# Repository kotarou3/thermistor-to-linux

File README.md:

# Thermistor to Linux adapter

This project creates three thermistor inputs that can be read via the Linux
hwmon interface

It uses the MAX6698 chip for its 3 thermistor inputs, attached to an I2C-Tiny-USB
via I2C, which then attaches onto the system USB bus

I chose the MAX6698 because it was one of the few chips satisfying:
 - Already has a Linux hwmon driver
 - Talks I2C/SMBus
 - Has dedicated thermistor inputs
 - Available via low MOQ suppliers like Digikey

Since few motherboards nowadays expose an I2C/SMBus bus on a header, it is further
adapted to USB via the I2C-Tiny-USB. It can then be plugged into a standard USB
port, or further adapted to an internal USB header

I personally created this because I wanted to monitor the coolant temperature
in my liquid cooling loop with hwmon, but I didn't have any motherboard thermistor
inputs

## Repository Guide
File                                                      | Purpose
----------------------------------------------------------|---------
`max6697-dkms/`                                           | DKMS module to build the hwmon kernel module for the MAX6698 if your kernel doesn't already include it
`thermistor-to-digispark-pcb/`                            | PCB for this project designed in KiCAD
`thermistor-to-digispark-pcb/gerber`                      | Gerber + drill + pick and place files (JLCPCB-compatible)
`thermistor-to-digispark-pcb/thermistor-to-digispark.csv` | Bill of materials (JLCPCB-compatible)
`thermistor-to-digispark-pcb/thermistor-to-digispark.pdf` | PDF schematic
`libsensors-max6698-sensors.conf`                         | libsensors config for more accurate readings and friendly names
`modprobe-max6698-sensors.conf`                           | modprobe config to blacklist `i2c-tiny-usb` autoloading for deterministic I2C bus numbering
`systemd-max6698-sensors.service`                         | systemd service to enable the MAX6698 device

## Hardware Setup
1. (Optional) Modify the divider resistors R3~R8 to suit your thermistor properties
   and measurement precision. Modify `libsensors-max6698-sensors.conf` to match
   (also contains information on how the default values were chosen)
2. Manufacture and assemble the PCB. Compiled gerber/drill/BOM/PnP files are
   already provided in a format suitable for JLCPCB. Not all parts might be
   available on JLCPCB though, so some manual assembly may be required.
3. Obtain a Digispark (clones available on Ebay) and [flash it with I2C-Tiny-USB
   firmware](https://github.com/harbaum/I2C-Tiny-USB/tree/master/digispark)
4. Attach the PCB to the Digispark via headers or otherwise
5. (Optional) Attach the Digispark to an USB-A to internal header adapter, if
   you wish to connect it to such a header
6. Attach your thermistors between the two pins of each `THERn` port

### MAX6698 Variants
There are multiple MAX6698 variants available. The files in this project assumes
the MAX6698UE38, which uses the TSSOP-16 footprint and I2C address `0x1c`

If you wish to use a different footprint variant, the PCB will need to be modified
to accommodate.  
If you wish to use a different I2C address variant, the addresses in
`libsensors-max6698-sensors.conf` and `systemd-max6698-sensors.service` need to
be updated

See the "Slave Address" table of the [MAX6698 datasheet](max6698-datasheet.pdf)
to see the corresponding part numbers

### BOM Cost

Notes:
- Prices in $USD at time of writing
- PCBA with JLCPCB, Digispark off Ebay@1/Digistump@5/JLCPCB@50, other parts off Digikey
- JLCPCB Assembly only includes the resistors and capacitors

Component            | Price@1 | Price@5 | Price@50
---------------------|---------|---------|----------
JLCPCB Manufacturing |  4      |  4      |  27.03
JLCPCB Assembly      |  9.02   |  9.02   |  11.29
JLCPCB Shipping      | 11      | 11      |  11
---------------------|---------|---------|----------
Digispark Clone      |  5.30   | 25      | 150
---------------------|---------|---------|----------
MAX6698UE38          |  7.58   | 37.90   | 326.56
Header Pins          |  0.33   |  1.02   |   8.63
Digikey Shipping     | 20      | 12      |   0
---------------------|---------|---------|----------
Total                | 57.23   | 99.94   | 534.51
Total (each)         | 57.23   | 19.99   |  10.70

Note that the project is not optimised for BOM cost, but ease of construction

An obvious way to reduce BOM cost significantly would be to do away with the
MAX6698 and Digispark, and use the ADC directly in an ATtiny or similar. But
that would mean spending time writing custom software (emulating a MAX6698, or
adding a new hwmon driver)

## Software Setup
Note: Instructions are for Debian bullseye on AMD64 and probably will need
modification for other distros or versions

1. Check if your kernel has the `max6697` module already (e.g., try running
   `sudo modprobe max6697`). If not, follow the DKMS instructions below
2. Run the below commands to install the various dependencies and config files

```sh
CONFIG_NAME="max6698-sensors"
sudo apt-get install -y lm-sensors
sudo install -m644 libsensors-max6698-sensors.conf "/etc/sensors.d/$CONFIG_NAME.conf"
sudo install -m644 modprobe-max6698-sensors.conf "/etc/modprobe.d/$CONFIG_NAME.conf"
sudo install -m644 systemd-max6698-sensors.service "/etc/systemd/system/$CONFIG_NAME.service"
sudo systemctl enable "$CONFIG_NAME.service"
sudo systemctl start "$CONFIG_NAME.service"
```

### DKMS Setup
The MAX6698 hwmon kernel module is included as part of `max6697`. However as of
writing, this module isn't included by default in Debian kernels, so must be
built out-of-tree unless you want to compile your own kernel

A DKMS module is provided that will automatically compile and install the
`max6697` module from the `linux-source` APT package. Run the commands below:

```sh
sudo apt-get install -y dkms linux-headers-amd64 linux-source
sudo dkms add max6697-dkms
sudo dkms install max6697/latest
```

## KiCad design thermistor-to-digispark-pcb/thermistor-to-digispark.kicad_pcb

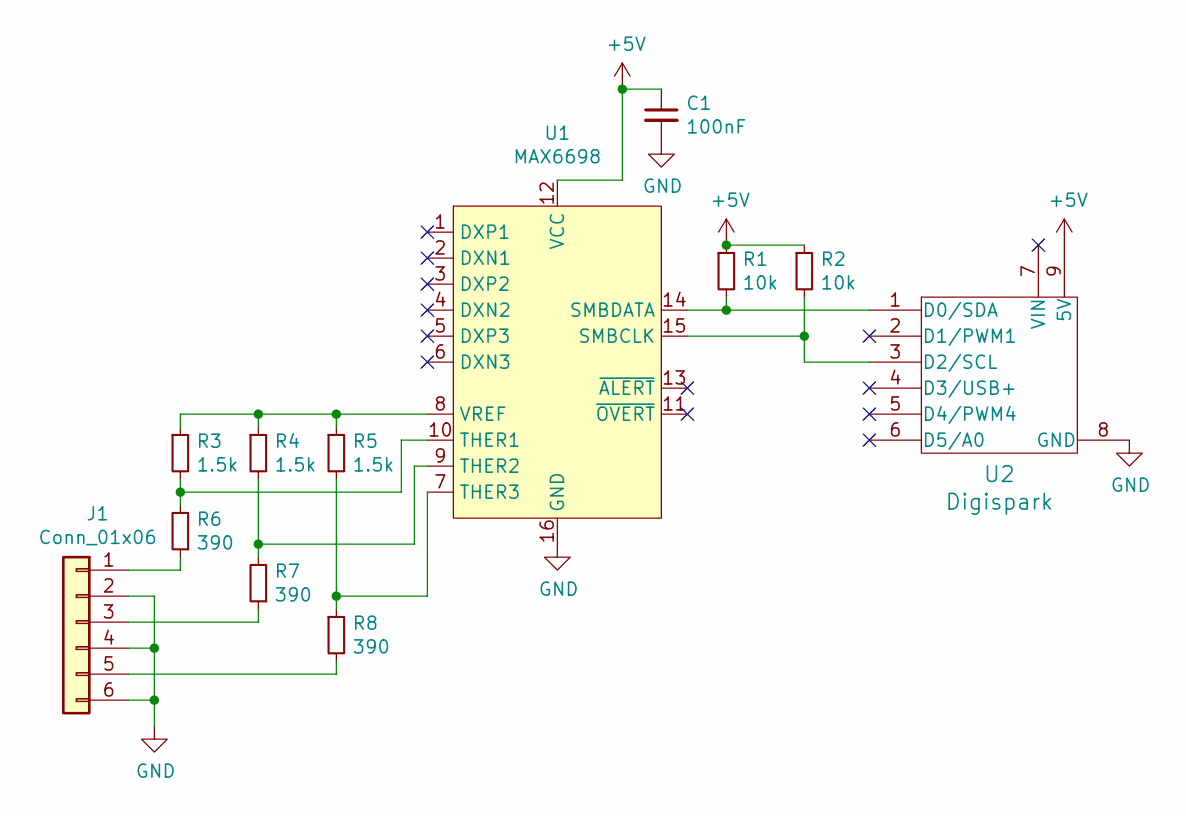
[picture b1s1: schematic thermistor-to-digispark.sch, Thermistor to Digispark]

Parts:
C1: 100nF; C_0603_1608Metric
J1: Conn_01x06; PinHeader_1x06_P2.54mm_Vertical
R1, R2: 10k; R_0603_1608Metric
R3, R4, R5: 1.5k; R_0603_1608Metric_Pad1.05x0.95mm_HandSolder
R6, R7, R8: 390; R_0603_1608Metric_Pad1.05x0.95mm_HandSolder
U1: MAX6698; TSSOP-16_4.4x5mm_P0.65mm
U2: Digispark; digispark

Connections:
+5V: C1.1, R1.1, R2.1, U1.12 (VCC), U2.9 (5V)
GND: C1.2, J1.2, J1.4, J1.6, U1.16 (GND), U2.8 (GND)
unnamed: J1.1, R6.1
unnamed: J1.3, R7.1
unnamed: J1.5, R8.2
unnamed: R1.2, U1.14 (SMBDATA), U2.1 (D0/SDA)
unnamed: R2.2, U1.15 (SMBCLK), U2.3 (D2/SCL)
unnamed: R3.1, R4.1, R5.1, U1.8 (VREF)
unnamed: R3.2, R6.2, U1.10 (THER1)
unnamed: R4.2, R7.2, U1.9 (THER2)
unnamed: R5.2, R8.1, U1.7 (THER3)

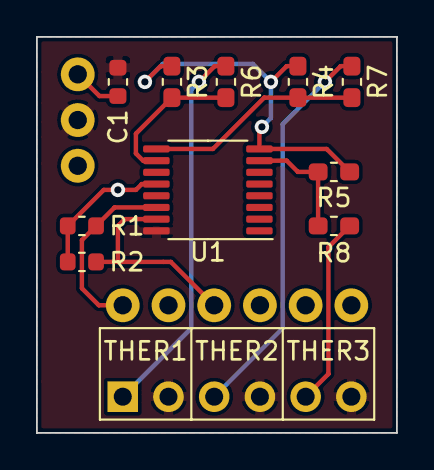
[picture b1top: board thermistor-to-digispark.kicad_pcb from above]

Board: 2 copper layers, 20.0 x 22.0 mm, 12 parts (0 on the bottom side), 11 nets.

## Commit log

2021-07-01 v1: Initial commit
2025-04-15 v1.1: Make some configs more reliable and use better resistance values
    - Wait for i2c-tiny-usb to load before registering the MAX6698
    - Close stdin when building the kernel module to prevent hanging on input
    - Updated resistance values improve measurement precision
